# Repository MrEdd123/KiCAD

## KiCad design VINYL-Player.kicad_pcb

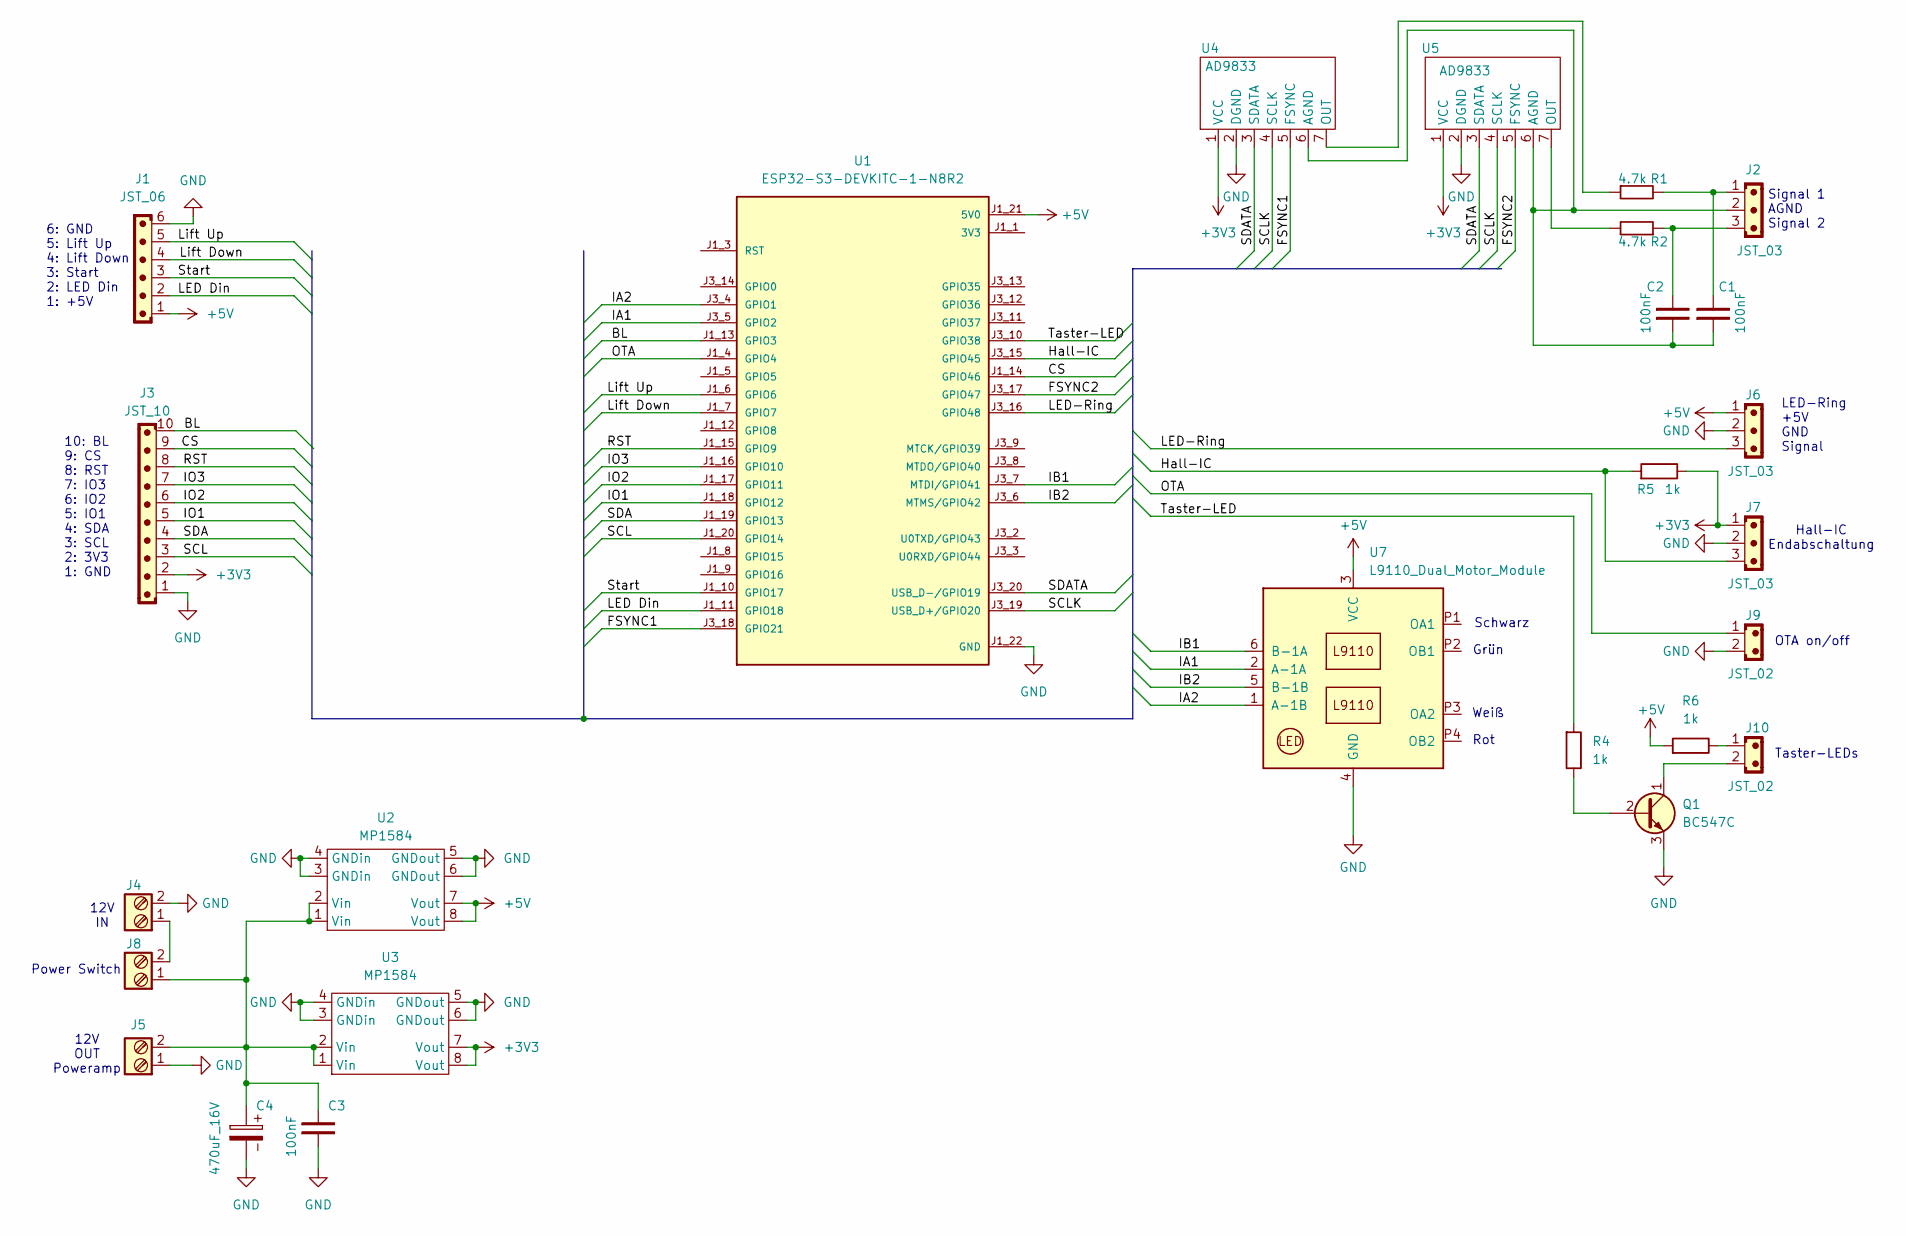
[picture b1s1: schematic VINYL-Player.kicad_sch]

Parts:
C1, C2, C3: 100nF; C_Disc_D5.0mm_W2.5mm_P2.50mm
C4: 470uF_16V; CP_Radial_D8.0mm_P3.50mm
J1: JST_06; JST_EH_B6B-EH-A_1x06_P2.50mm_Vertical
J2, J6, J7: JST_03; JST_EH_B3B-EH-A_1x03_P2.50mm_Vertical
J3: JST_10; JST_EH_B10B-EH-A_1x10_P2.50mm_Vertical
J4, J5, J8: Screw_Terminal_2_P5.00mm; TerminalBlock_Phoenix_PT-1,5-2-5.0-H_1x02_P5.00mm_Horizontal
J9, J10: JST_02; JST_EH_B2B-EH-A_1x02_P2.50mm_Vertical
Q1: BC547C; TO-92_Inline_Wide_CBE
R1, R2: 4.7k; R_Axial_DIN0207_L6.3mm_D2.5mm_P10.16mm_Horizontal
R4, R5, R6: 1k; R_Axial_DIN0204_L3.6mm_D1.6mm_P7.62mm_Horizontal
U1: ESP32-S3-DEVKITC-1-N8R2; XCVR_ESP32-S3-DEVKITC-1-N8R2; PARTREV V1
U2, U3: MP1584; MP1584-PowerDown-Modul
U4, U5: AD9833; AD9833-Modul-Hochkant
U7: L9110_Dual_Motor_Module

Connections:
3V3: U1.J1_1 (3V3), U1.J1_2 (3V3)
+3V3: J3.2, J7.1, R5.2, U3.7 (Vout), U3.8 (Vout), U4.1 (VCC), U5.1 (VCC)
+5V: J1.1, J6.1, R6.1, U1.J1_21 (5V0), U2.7 (Vout), U2.8 (Vout), U7.3 (VCC)
/<NO NET>: U1.J3_20 (USB_D-/GPIO19), U4.3 (SDATA), U5.3 (SDATA)
/BL: J3.10, U1.J1_13 (GPIO3)
/CS: J3.9, U1.J1_14 (GPIO46)
/FSYNC1: U1.J3_18 (GPIO21), U4.5 (FSYNC)
/FSYNC2: U1.J3_17 (GPIO47), U5.5 (FSYNC)
/Hall-IC: J7.3, R5.1, U1.J3_15 (GPIO45)
/IA1: U1.J3_5 (GPIO2), U7.2 (A-1A)
/IA2: U1.J3_4 (GPIO1), U7.1 (A-1B)
/IB1: U1.J3_7 (MTDI/GPIO41), U7.6 (B-1A)
/IB2: U1.J3_6 (MTMS/GPIO42), U7.5 (B-1B)
/IO1: J3.5, U1.J1_18 (GPIO12)
/IO2: J3.6, U1.J1_17 (GPIO11)
/IO3: J3.7, U1.J1_16 (GPIO10)
/LED Din: J1.2, U1.J1_11 (GPIO18)
/LED-Ring: J6.3, U1.J3_16 (GPIO48)
/Lift Down: J1.4, U1.J1_7 (GPIO7)
/Lift Up: J1.5, U1.J1_6 (GPIO6)
/OTA: J9.1, U1.J1_4 (GPIO4)
/RST: J3.8, U1.J1_15 (GPIO9)
/SCL: J3.3, U1.J1_20 (GPIO14)
/SCLK: U1.J3_19 (USB_D+/GPIO20), U4.4 (SCLK), U5.4 (SCLK)
/SDA: J3.4, U1.J1_19 (GPIO13)
/Start: J1.3, U1.J1_10 (GPIO17)
/Taster-LED: R4.1, U1.J3_10 (GPIO38)
GND: C3.1, C4.2, J1.6, J3.1, J4.2, J5.1, J6.2, J7.2, J9.2, Q1.3 (E), U1.J1_22 (GND), U1.J3_1 (GND), U1.J3_21 (GND), U1.J3_22 (GND), U2.3 (GNDin), U2.4 (GNDin), U2.5 (GNDout), U2.6 (GNDout), U3.3 (GNDin), U3.4 (GNDin), U3.5 (GNDout), U3.6 (GNDout), U4.2 (DGND), U5.2 (DGND), U7.4 (GND)
unnamed: C1.2, J2.1, R1.2
unnamed: C2.2, J2.3, R2.1
unnamed: C3.2, C4.1, J5.2, J8.1, U2.1 (Vin), U2.2 (Vin), U3.1 (Vin), U3.2 (Vin)
unnamed: J4.1, J8.2
unnamed: J10.1, R6.2
unnamed: Q1.2 (B), R4.2
unnamed: J10.2, Q1.1 (C)
unnamed: C1.1, C2.1, J2.2, U4.6 (AGND), U5.6 (AGND)
unnamed: R1.1, U4.7 (OUT)
unnamed: R2.2, U5.7 (OUT)

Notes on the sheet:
Taster-LEDs
12V OUT Poweramp
Rot
Schwarz
Signal 1 AGND Signal 2
Grün
12V IN
6: GND 5: Lift Up 4: Lift Down 3: Start 2: LED Din 1: +5V
Power Switch
10: BL 9: CS 8: RST 7: IO3 6: IO2 5: IO1 4: SDA 3: SCL 2: 3V3 1: GND
LED-Ring +5V GND Signal
Weiß
OTA on/off
Hall-IC Endabschaltung

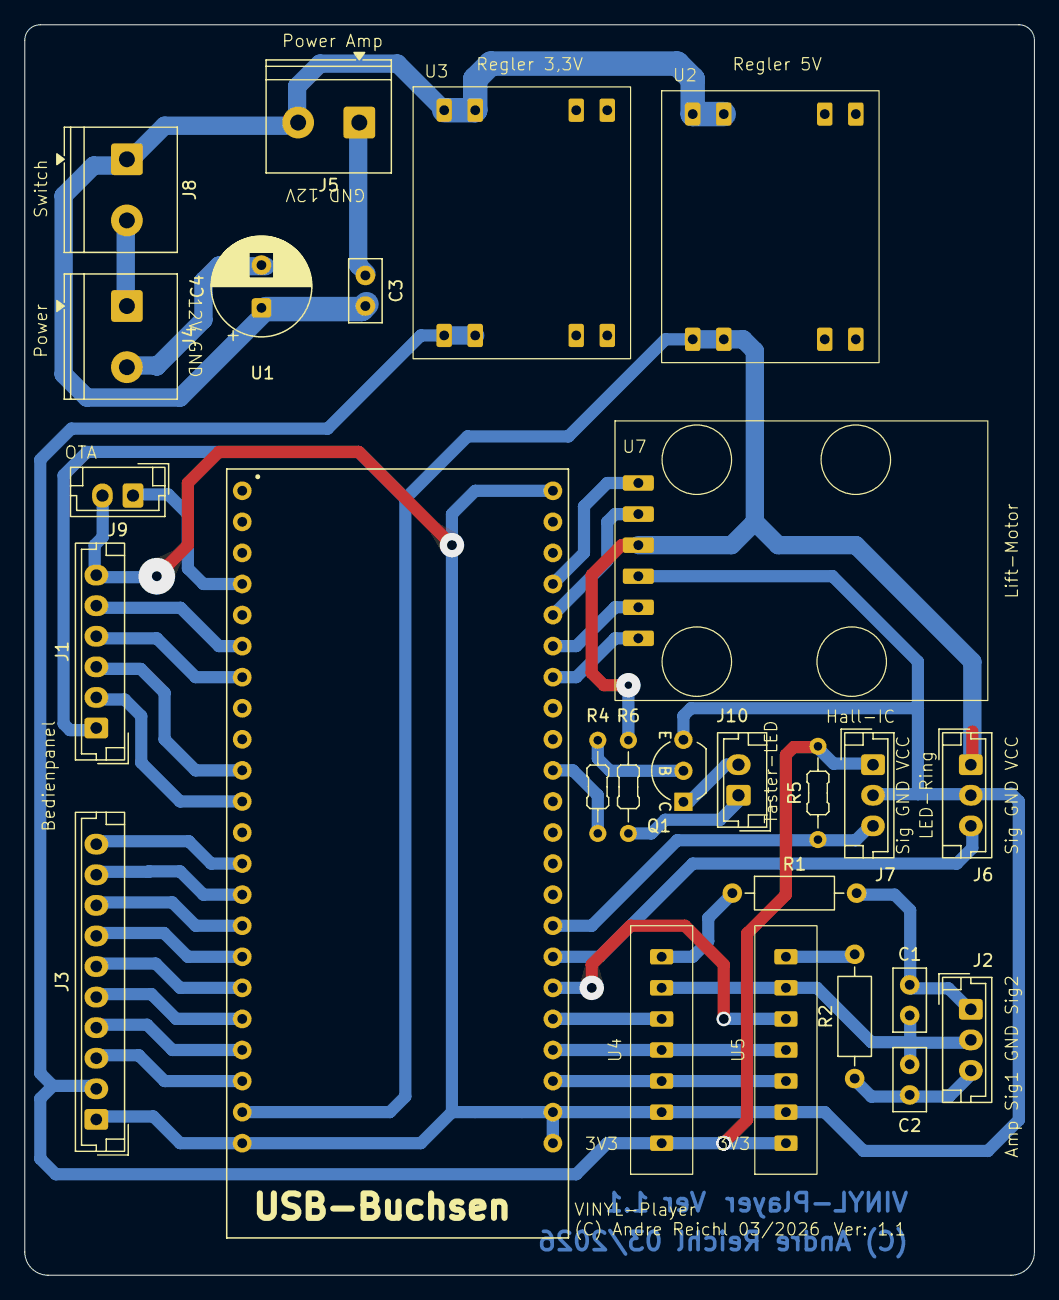
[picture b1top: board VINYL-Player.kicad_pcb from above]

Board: 2 copper layers, 82.5 x 102.2 mm, 26 parts (0 on the bottom side), 38 nets.
